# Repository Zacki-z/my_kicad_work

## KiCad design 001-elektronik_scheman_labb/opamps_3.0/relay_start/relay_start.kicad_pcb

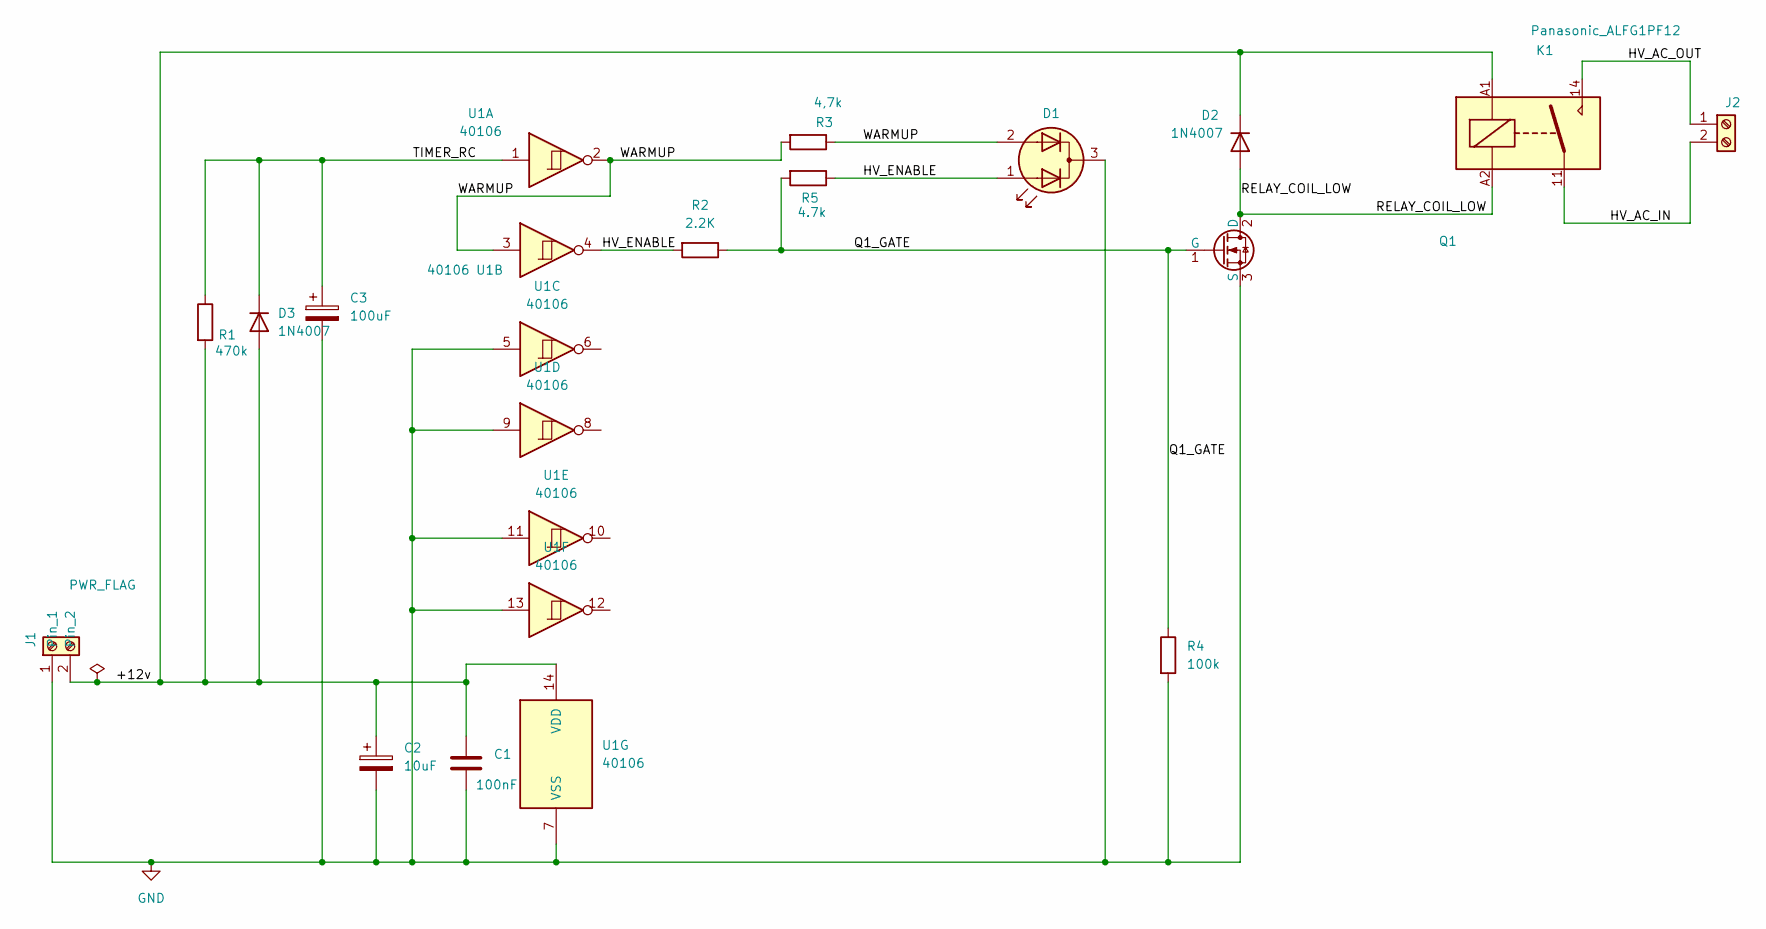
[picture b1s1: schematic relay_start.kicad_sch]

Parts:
C1: 100nF; CP_Radial_D5.0mm_P2.50mm
C2: 10uF; CP_Radial_D8.0mm_P3.50mm
C3: 100uF; CP_Radial_D8.0mm_P3.50mm
D1: LED_D5.0mm-3
D2, D3: 1N4007; D_DO-41_SOD81_P10.16mm_Horizontal
J1, J2: Screw_Terminal_01x02; TerminalBlock_MaiXu_MX126-5.0-02P_1x02_P5.00mm
K1: Panasonic_ALFG1PF12; Relay_SPST_Panasonic_ALFG_FormA_CircularHoles
Q1: Q_NMOS_GDS; TO-92
R1: 470k; R_Axial_DIN0207_L6.3mm_D2.5mm_P7.62mm_Horizontal
R2: 2.2K; R_Axial_DIN0207_L6.3mm_D2.5mm_P7.62mm_Horizontal
R3: 4,7k; R_Axial_DIN0207_L6.3mm_D2.5mm_P7.62mm_Horizontal
R4: 100k; R_Axial_DIN0207_L6.3mm_D2.5mm_P7.62mm_Horizontal
R5: 4.7k; R_Axial_DIN0207_L6.3mm_D2.5mm_P7.62mm_Horizontal
U1: 40106; CERDIP-14_W7.62mm_SideBrazed

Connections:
/+12v: C1.1, C2.1, D2.1 (K), D3.2 (A), J1.2, K1.A1, R1.2, U1.14 (VDD)
/HV_AC_IN: J2.2, K1.11
/HV_AC_OUT: J2.1, K1.14
/HV_ENABLE: D1.1 (A1), R2.2, R5.1, U1.4
/Q1_GATE: Q1.1 (G), R2.1, R4.1, R5.2
/RELAY_COIL_LOW: D2.2 (A), K1.A2, Q1.2 (D)
/TIMER_RC: C3.1, D3.1 (K), R1.1, U1.1
/WARMUP: D1.2 (A2), R3.1, R3.2, U1.2, U1.3
GND: C1.2, C2.2, C3.2, D1.3 (K), J1.1, Q1.3 (S), R4.2, U1.5, U1.7 (VSS), U1.9, U1.11, U1.13

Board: 2 copper layers, 16 parts (0 on the bottom side), 9 nets, no tracks yet.

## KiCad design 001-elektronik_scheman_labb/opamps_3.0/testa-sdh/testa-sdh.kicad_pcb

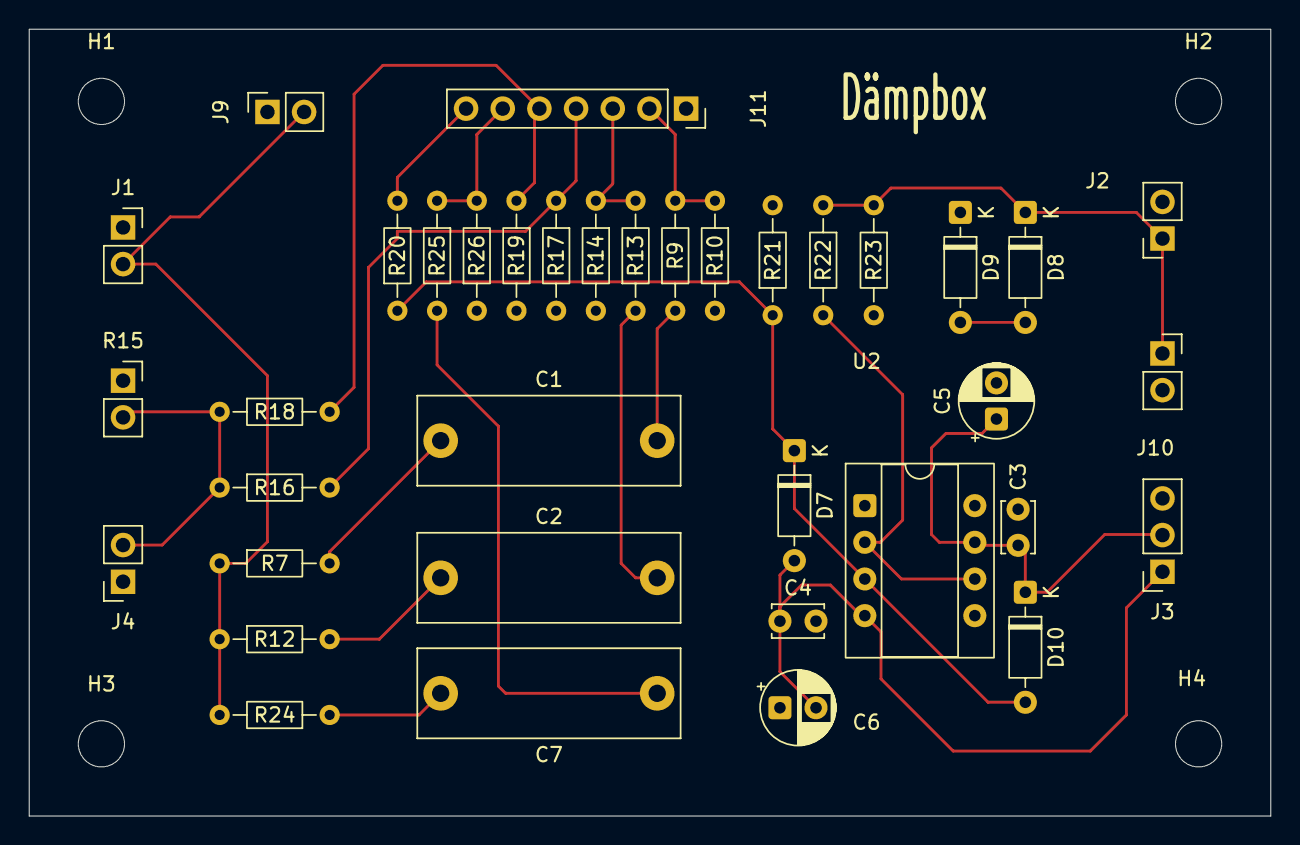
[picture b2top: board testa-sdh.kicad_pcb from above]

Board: 2 copper layers, 86.0 x 54.5 mm, 41 parts (0 on the bottom side), 21 nets.

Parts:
C1, C2: 100 nF 630v; C_Rect_L18.0mm_W6.0mm_P15.00mm_FKS3_FKP3
C3, C4: 100 nF; C_Disc_D3.4mm_W2.1mm_P2.50mm
C5, C6: 10 uF; CP_Radial_D5.0mm_P2.50mm
C7: 100 nF 630V; C_Rect_L18.0mm_W6.0mm_P15.00mm_FKS3_FKP3
D7, D10: 1N4148; D_DO-35_SOD27_P7.62mm_Horizontal
D8, D9: BZX55C5V1; D_DO-35_SOD27_P7.62mm_Horizontal
H1, H2, H3, H4: MountingHole; MountingHole_3.2mm_M3
J1: Test_probe; PinSocket_1x02_P2.54mm_Vertical
J2: TO_Focusrite_input; PinSocket_1x02_P2.54mm_Vertical
J3: OP_AMP_PWR; PinSocket_1x03_P2.54mm_Vertical
J4: Speaker; PinSocket_1x02_P2.54mm_Vertical
J9, J10: Mätinstrument; PinSocket_1x02_P2.54mm_Vertical
J11: J_SW_SIGNAL; PinSocket_1x07_P2.54mm_Vertical
R7, R12, R21, R26: 1M; R_Axial_DIN0204_L3.6mm_D1.6mm_P7.62mm_Horizontal
R9, R13: 953k; R_Axial_DIN0204_L3.6mm_D1.6mm_P7.62mm_Horizontal
R10: 20K; R_Axial_DIN0204_L3.6mm_D1.6mm_P7.62mm_Horizontal
R14: 274k; R_Axial_DIN0204_L3.6mm_D1.6mm_P7.62mm_Horizontal
R15: 8 50W; PinSocket_1x02_P2.54mm_Vertical
R16, R23: 100k; R_Axial_DIN0204_L3.6mm_D1.6mm_P7.62mm_Horizontal
R17: 1k; R_Axial_DIN0204_L3.6mm_D1.6mm_P7.62mm_Horizontal
R18: 90,9k; R_Axial_DIN0204_L3.6mm_D1.6mm_P7.62mm_Horizontal
R19: 10k; R_Axial_DIN0204_L3.6mm_D1.6mm_P7.62mm_Horizontal
R20: 20k; R_Axial_DIN0204_L3.6mm_D1.6mm_P7.62mm_Horizontal
R22: 330R; R_Axial_DIN0204_L3.6mm_D1.6mm_P7.62mm_Horizontal
R24, R25: 10K; R_Axial_DIN0204_L3.6mm_D1.6mm_P7.62mm_Horizontal
U2: OPA134; CERDIP-8_W7.62mm_SideBrazed_Socket

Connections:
/INTPUT: J1.2, J9.2, R7.1, R12.1, R24.2
/INT_1_10: C2.1, R12.2
/INT_1_10_OUT: J11.3, R13.2, R14.1
/INT_1_100: C1.1, R7.2
/INT_1_100_OUT: J11.2, R9.2, R10.1
/LOW_1_1: C7.2, R24.1
/LOW_1_1_OUT: J11.6, R25.1, R26.2
/SPK_1_10_OUT: J11.5, R18.2, R19.1
/SPK_1_100: J4.2, R15.2, R16.1, R18.1
/SPK_1_100_OUT: J11.4, R16.2, R17.1
/sound-card/12V+: C3.1, C5.1, D10.1 (K), J3.2, U2.7 (V+)
/sound-card/12V-: C4.1, C6.2, D7.2 (A), J3.1, U2.4 (V-)
/sound-card/OP_AMP_OUT: R22.2, U2.2 (-), U2.6
/sound-card/audio_out: D8.1 (K), J2.1, J10.1, R22.1, R23.1
MEASURE_GND: C3.2, C4.2, C5.2, C6.1, D9.1 (K), J1.1, J2.2, J3.3, J4.1, J9.1, J10.2, R10.2, R14.2, R15.1, R17.2, R19.2, R21.2, R23.2, R26.1
MEASURE_SIGNAL: J11.7, R20.2
unnamed: C1.2, R9.1
unnamed: C2.2, R13.1
unnamed: C7.1, R25.2
unnamed: D8.2 (A), D9.2 (A)
unnamed: D7.1 (K), D10.2 (A), R20.1, R21.1, U2.3 (+)

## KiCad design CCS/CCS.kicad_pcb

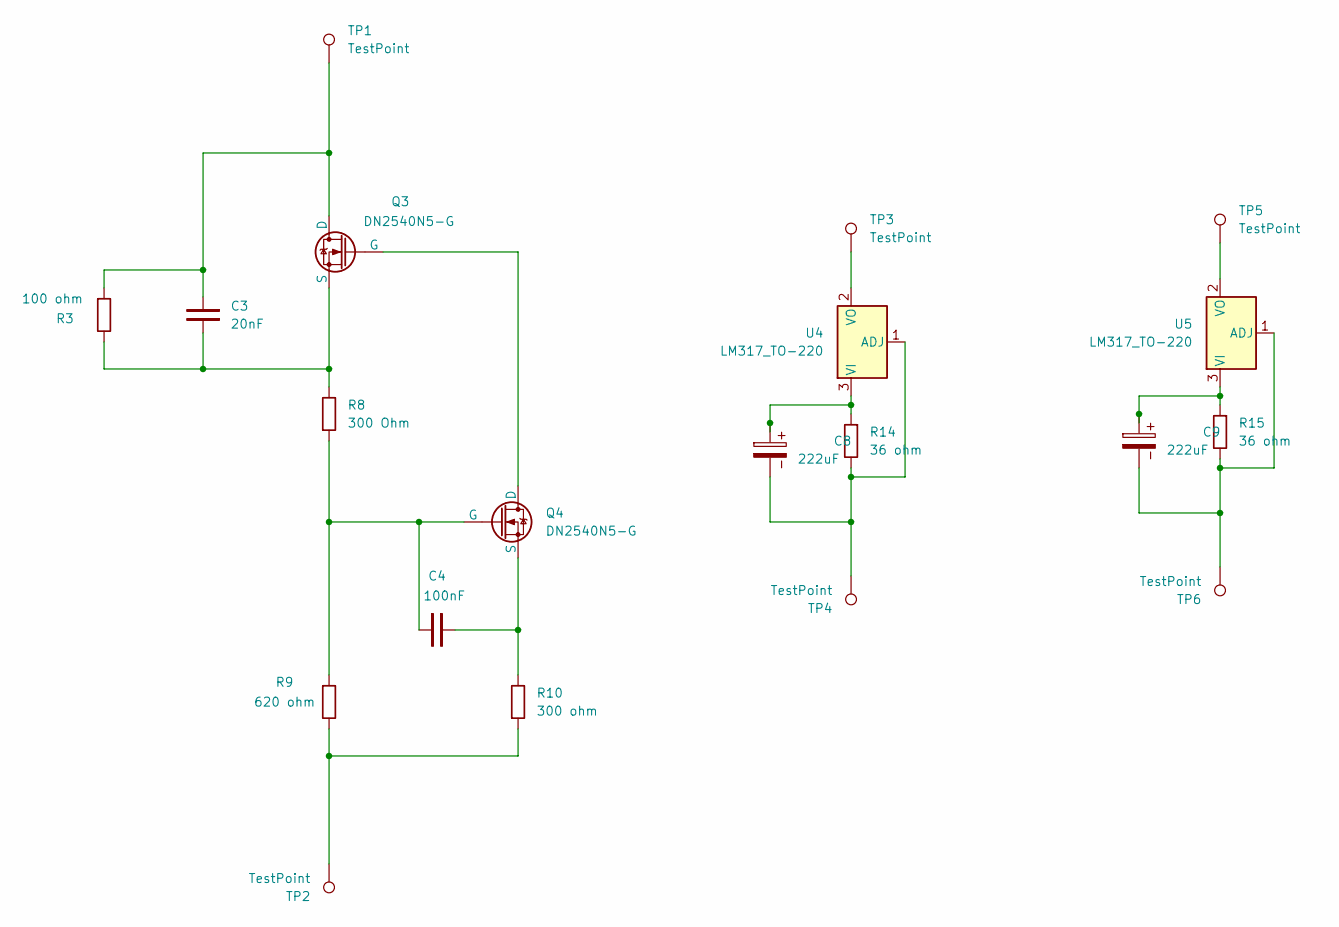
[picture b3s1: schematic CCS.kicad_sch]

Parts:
C3: 20nF; C_Disc_D3.0mm_W2.0mm_P2.50mm
C4: 100nF; C_Disc_D3.0mm_W2.0mm_P2.50mm
C8, C9: 222uF; CP_Radial_D5.0mm_P2.00mm
Q3, Q4: DN2540N5-G; TO-220-3_Vertical
R3: 100 ohm; R_Axial_DIN0207_L6.3mm_D2.5mm_P10.16mm_Horizontal
R8: 300 Ohm; R_Axial_DIN0207_L6.3mm_D2.5mm_P10.16mm_Horizontal
R9: 620 ohm; R_Axial_DIN0207_L6.3mm_D2.5mm_P10.16mm_Horizontal
R10: 300 ohm; R_Axial_DIN0207_L6.3mm_D2.5mm_P10.16mm_Horizontal
R14, R15: 36 ohm; R_Axial_DIN0207_L6.3mm_D2.5mm_P10.16mm_Horizontal
TP1, TP2, TP3, TP4, TP5, TP6: TestPoint; Pin_D1.3mm_L10.0mm_W3.5mm_Flat
U4, U5: LM317_TO-220; TO-220-3_Vertical

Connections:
unnamed: C3.1, Q3.2 (D), R3.1, TP1.1
unnamed: Q3.1 (G), Q4.2 (D)
unnamed: C3.2, Q3.3 (S), R3.2, R8.2
unnamed: C4.1, Q4.1 (G), R8.1, R9.1
unnamed: C4.2, Q4.3 (S), R10.2
unnamed: R9.2, R10.1, TP2.1
unnamed: C8.2, R14.2, TP4.1, U4.1 (ADJ)
unnamed: C8.1, R14.1, U4.3 (VI)
unnamed: TP3.1, U4.2 (VO)
unnamed: C9.2, R15.2, TP6.1, U5.1 (ADJ)
unnamed: C9.1, R15.1, U5.3 (VI)
unnamed: TP5.1, U5.2 (VO)

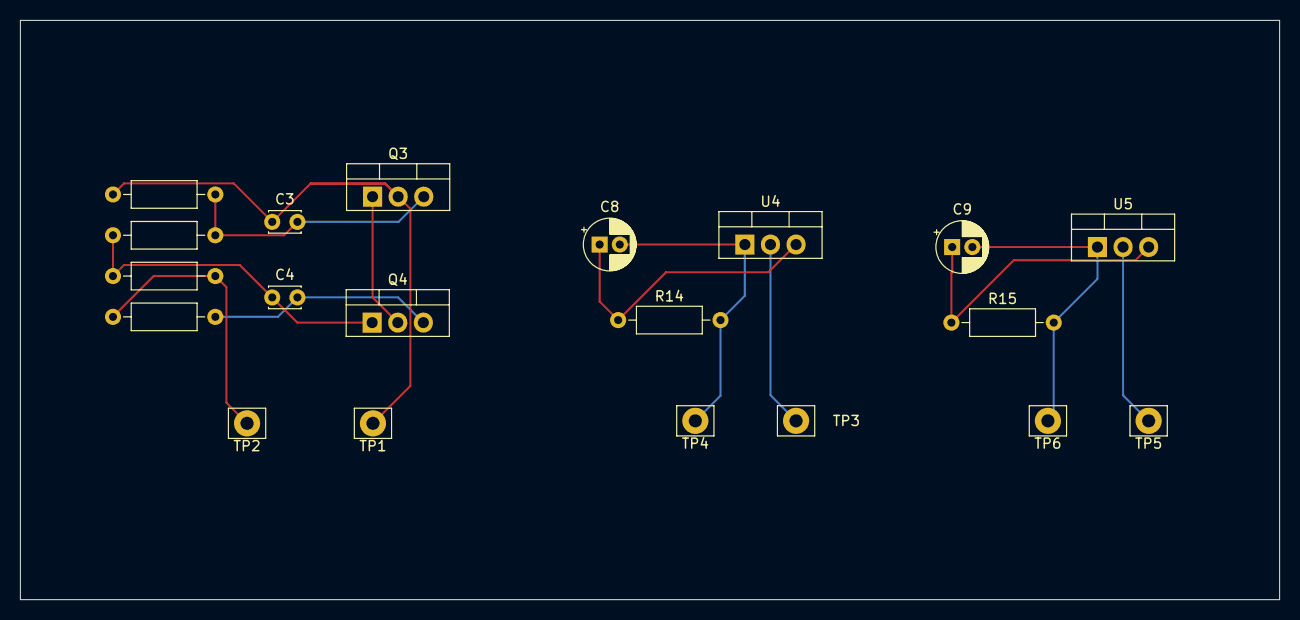
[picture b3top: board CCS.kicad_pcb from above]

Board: 2 copper layers, 125.0 x 57.5 mm, 20 parts (0 on the bottom side), 12 nets.

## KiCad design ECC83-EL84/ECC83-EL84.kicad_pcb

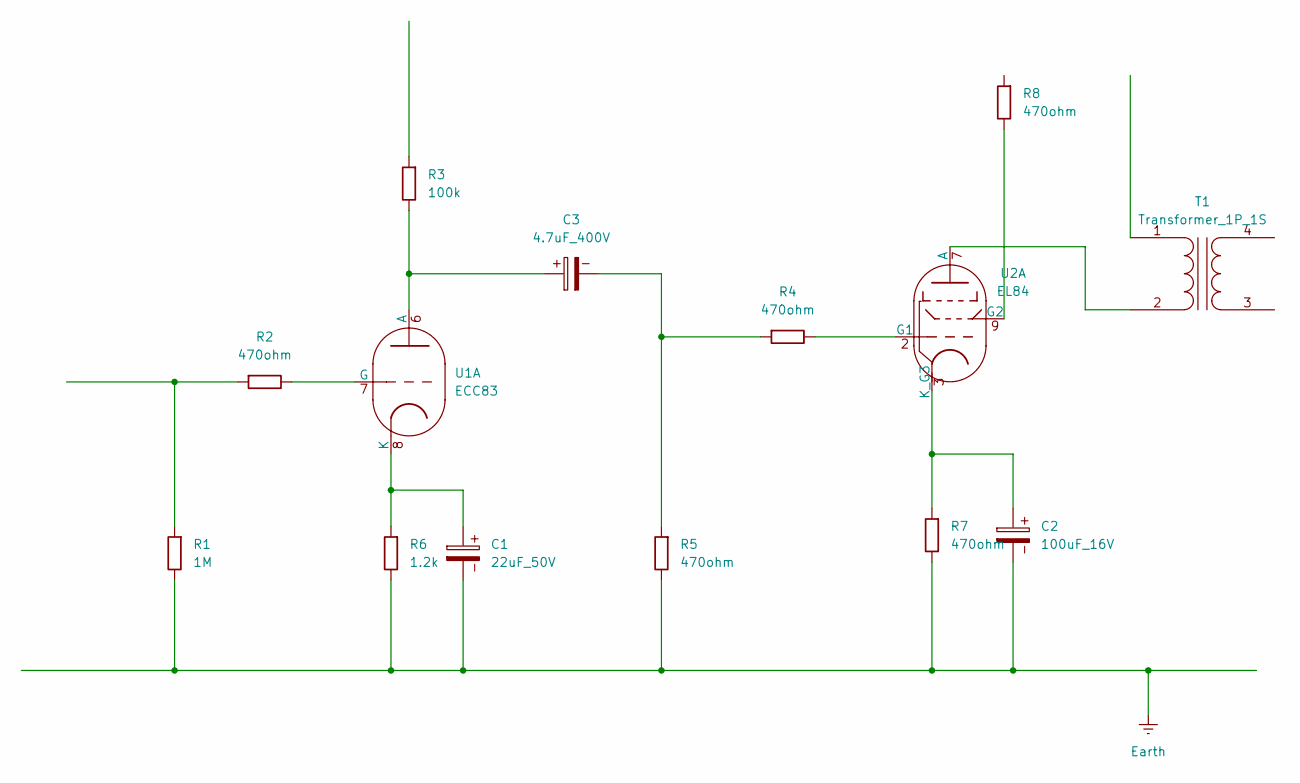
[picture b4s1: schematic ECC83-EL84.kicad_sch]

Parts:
C1: 22uF_50V; CP_Radial_D5.0mm_P2.00mm
C2: 100uF_16V; CP_Radial_D5.0mm_P2.00mm
C3: 4.7uF_400V; CP_Radial_D10.0mm_P5.00mm
R1: 1M; R_Axial_DIN0207_L6.3mm_D2.5mm_P10.16mm_Horizontal
R2, R4, R5, R7, R8: 470ohm; R_Axial_DIN0207_L6.3mm_D2.5mm_P10.16mm_Horizontal
R3: 100k; R_Axial_DIN0207_L6.3mm_D2.5mm_P10.16mm_Horizontal
R6: 1.2k; R_Axial_DIN0207_L6.3mm_D2.5mm_P10.16mm_Horizontal
T1: Transformer_1P_1S
U1: ECC83; Valve_Noval_P
U2: EL84; Valve_Noval_P

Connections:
Earth: C1.2, C2.2, R1.2, R5.2, R6.2, R7.2
unnamed: C3.2, R4.1, R5.1
unnamed: R1.1, R2.1
unnamed: T1.2 (AB), U2.7 (A)
unnamed: C3.1, R3.2, U1.6 (A)
unnamed: R2.2, U1.7 (G)
unnamed: C1.1, R6.1, U1.8 (K)
unnamed: R4.2, U2.2 (G1)
unnamed: R8.2, U2.9 (G2)
unnamed: C2.1, R7.1, U2.3 (K_G3)

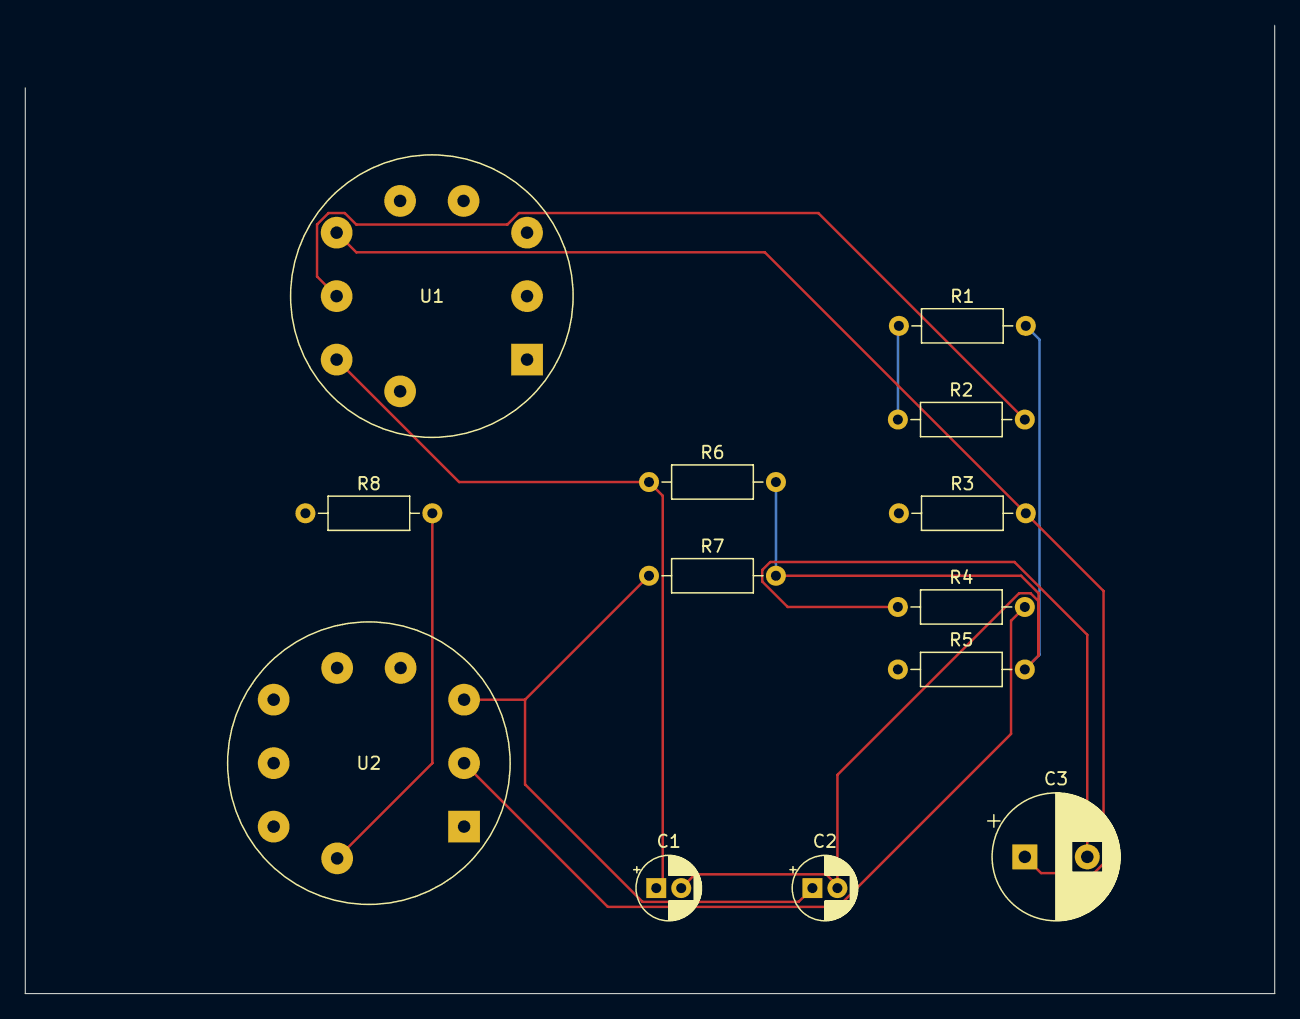
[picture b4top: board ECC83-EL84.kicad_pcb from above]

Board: 2 copper layers, 100.0 x 77.5 mm, 13 parts (0 on the bottom side), 9 nets.

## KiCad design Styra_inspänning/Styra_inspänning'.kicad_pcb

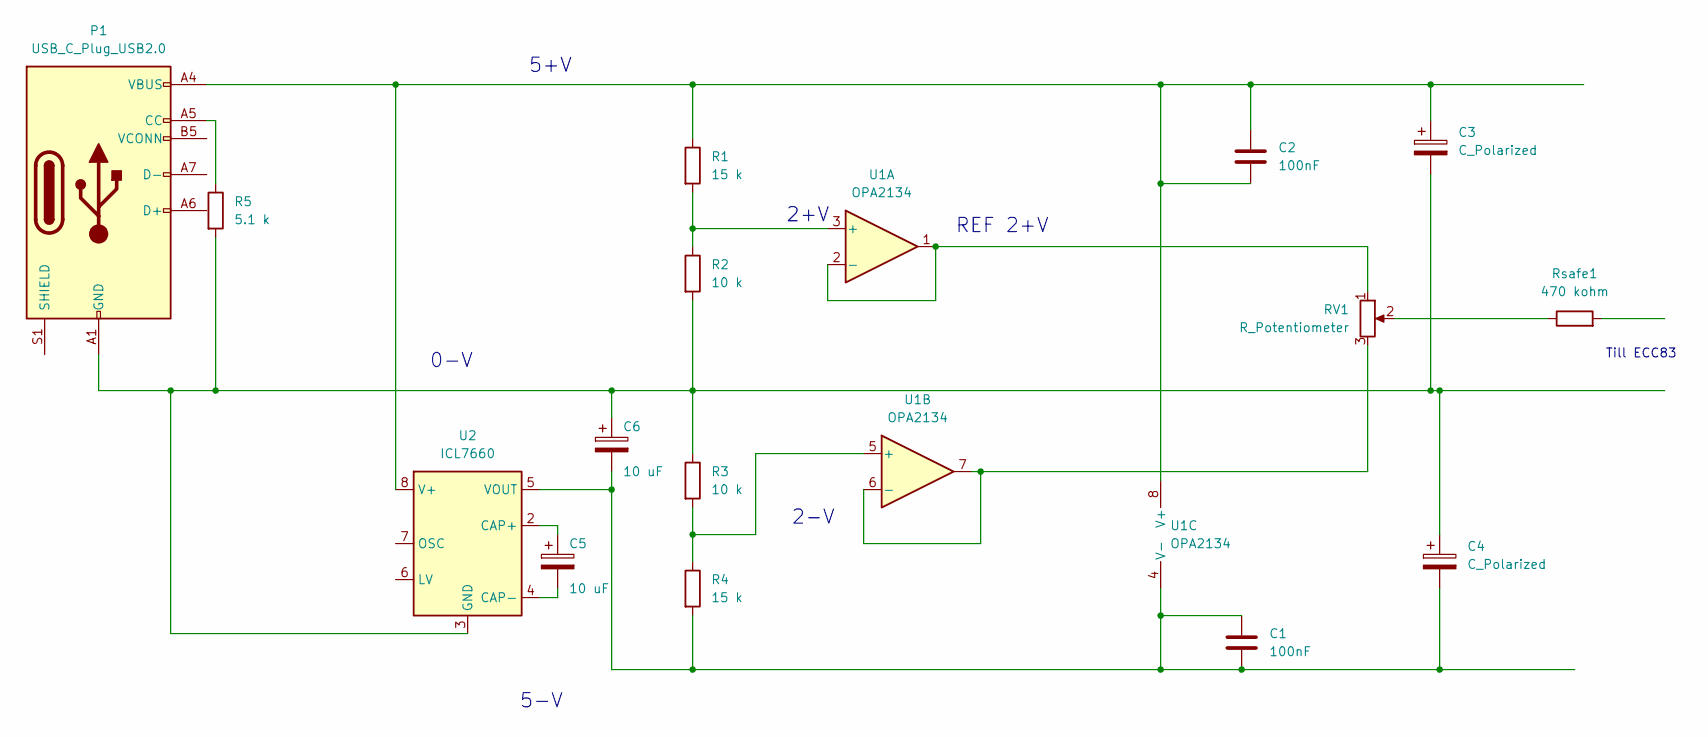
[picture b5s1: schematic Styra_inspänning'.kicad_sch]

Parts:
C1, C2: 100nF; CP_Radial_D13.0mm_P7.50mm
C3, C4: C_Polarized; CP_Radial_D13.0mm_P7.50mm
C5, C6: 10 uF; CP_Radial_D13.0mm_P7.50mm
P1: USB_C_Plug_USB2.0; USB_C_Receptacle_Amphenol_124019772112A
R1, R4: 15 k; R_Axial_DIN0614_L14.3mm_D5.7mm_P15.24mm_Horizontal
R2, R3: 10 k; R_Axial_DIN0614_L14.3mm_D5.7mm_P15.24mm_Horizontal
R5: 5.1 k; R_Axial_DIN0614_L14.3mm_D5.7mm_P15.24mm_Horizontal
RV1: R_Potentiometer; Potentiometer_Bourns_3266Z_Horizontal
Rsafe1: 470 kohm; R_Axial_DIN0614_L14.3mm_D5.7mm_P15.24mm_Horizontal
U1: OPA2134; DIP-8_W10.16mm
U2: ICL7660; DIP-8_W10.16mm

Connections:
unnamed: P1.A5 (CC), R5.1
unnamed: RV1.2, Rsafe1.1
unnamed: R1.2, R2.1, U1.3 (+)
unnamed: RV1.1, U1.1, U1.2 (-)
unnamed: R3.2, R4.1, U1.5 (+)
unnamed: RV1.3, U1.6 (-), U1.7
unnamed: C2.1, C2.2, C3.1, P1.A4 (VBUS), P1.A9 (VBUS), P1.B4 (VBUS), P1.B9 (VBUS), R1.1, U1.8 (V+), U2.8 (V+)
unnamed: C1.1, C1.2, C4.2, C6.2, R4.2, U1.4 (V-), U2.5 (VOUT)
unnamed: C5.1, U2.2 (CAP+)
unnamed: C5.2, U2.4 (CAP-)
unnamed: C3.2, C4.1, C6.1, P1.A1 (GND), P1.A12 (GND), P1.B1 (GND), P1.B12 (GND), R2.2, R3.1, R5.2, U2.3 (GND)

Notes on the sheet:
2-V
5+V
0-V
2+V
Till ECC83
5-V
REF 2+V

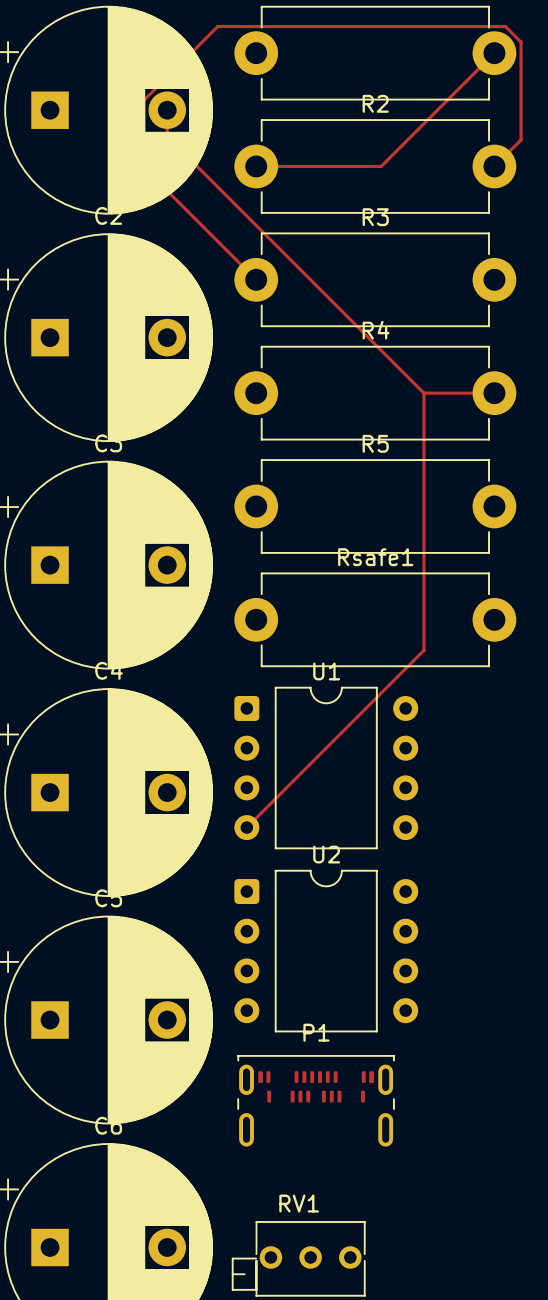
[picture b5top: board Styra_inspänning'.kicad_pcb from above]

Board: 2 copper layers, 16 parts (0 on the bottom side), 11 nets.

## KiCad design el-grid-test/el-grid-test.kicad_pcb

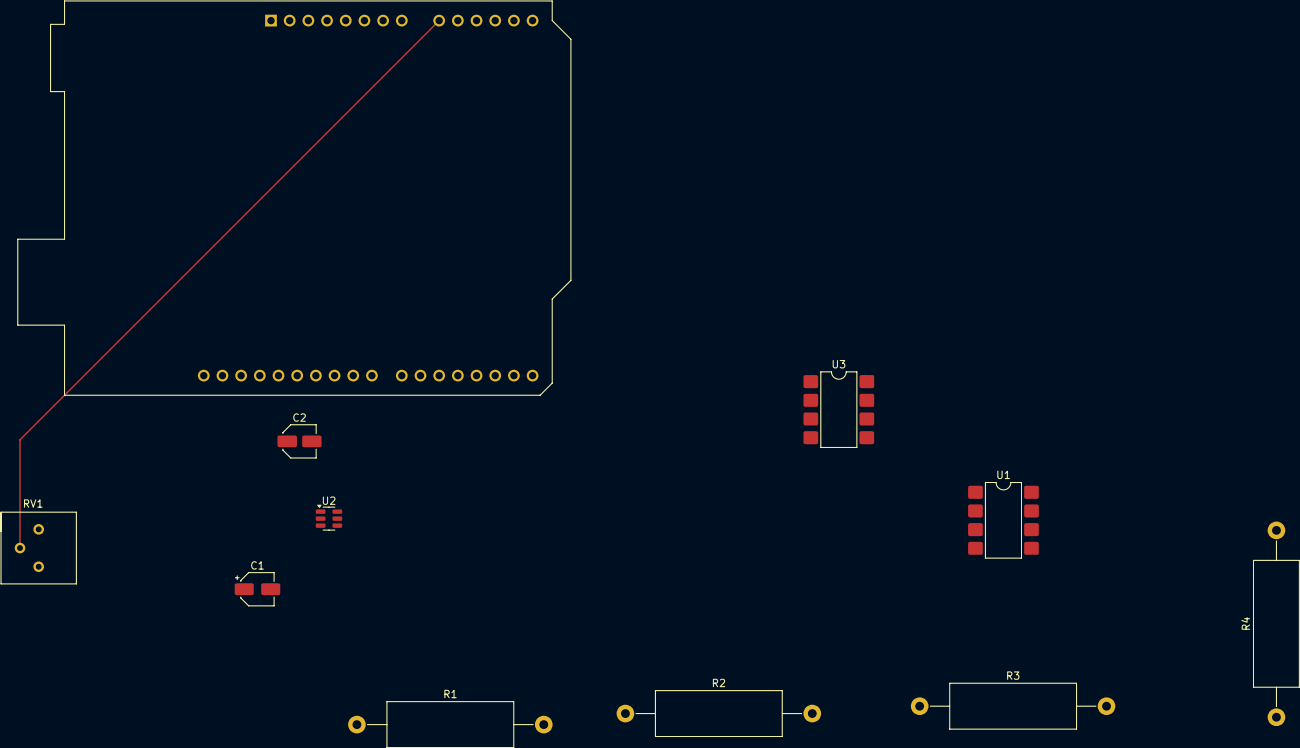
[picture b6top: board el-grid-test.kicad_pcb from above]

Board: 2 copper layers, 11 parts (0 on the bottom side), 13 nets.

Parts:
A1: Arduino_UNO_R3
C1: 10 uf; CP_Elec_4x5.8
C2: 10 uf; C_Elec_4x5.4
R1, R2, R3, R4: 10k; R_Axial_DIN0617_L17.0mm_D6.0mm_P25.40mm_Horizontal
RV1: R_Potentiometer; Potentiometer_Bourns_3296P_Horizontal
U1: TL072; SMDIP-8_W7.62mm
U2: MCP4725xxx-xCH; SOT-23-6
U3: ICL7660; SMDIP-8_W7.62mm

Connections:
Earth: A1.7 (GND), C2.2, R4.1, RV1.3, U2.2 (VSS), U3.3 (GND)
unnamed: A1.5 (+5V), R3.2, RV1.1, U1.8 (V+), U2.3 (VDD), U3.8 (V+)
unnamed: A1.9 (A0), RV1.2
unnamed: R2.1, U1.1
unnamed: U1.3 (+), U1.6 (-), U1.7
unnamed: R1.1, R2.2, U1.2 (-)
unnamed: R3.1, R4.2, U1.5 (+)
unnamed: C2.1, U1.4 (V-), U3.5 (VOUT)
unnamed: A1.14 (SCL/A5), U2.5 (SCL)
unnamed: A1.13 (SDA/A4), U2.4 (SDA)
unnamed: R1.2, U2.1 (VOUT)
unnamed: C1.1, U3.2 (CAP+)
unnamed: C1.2, U3.4 (CAP-)

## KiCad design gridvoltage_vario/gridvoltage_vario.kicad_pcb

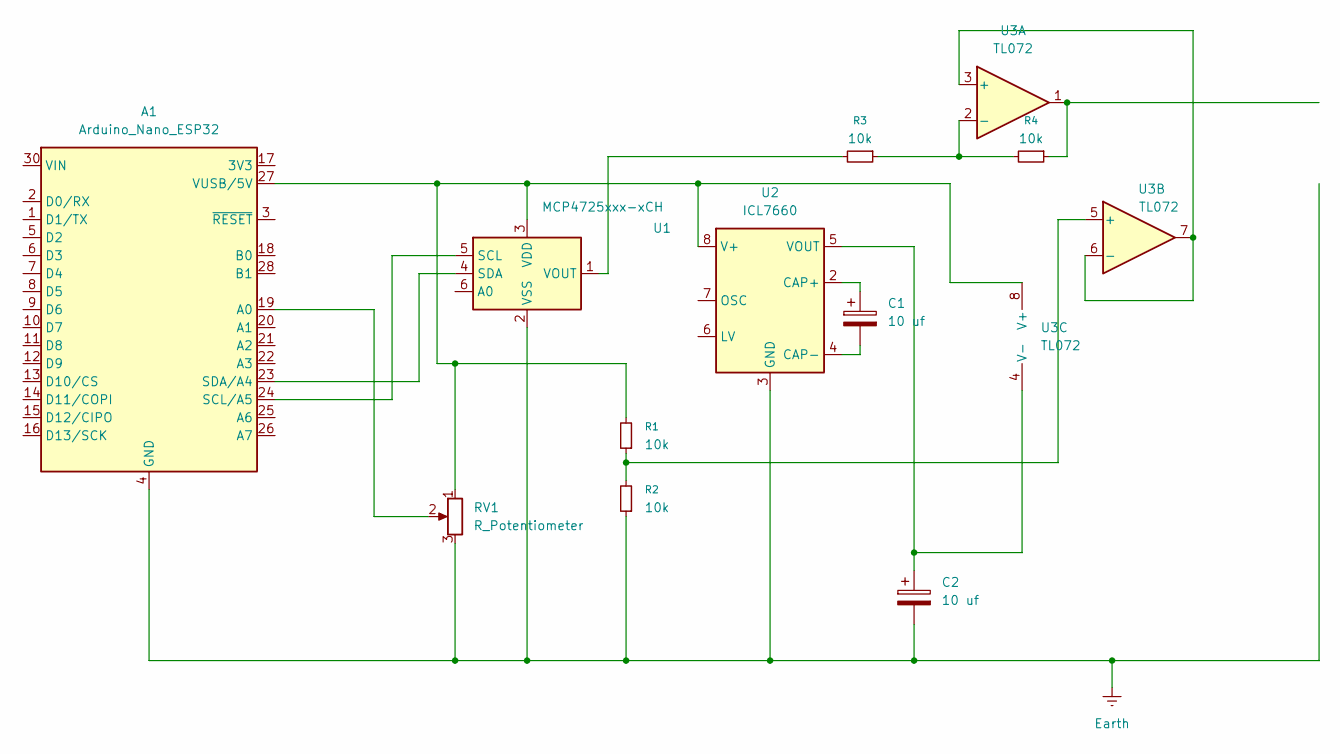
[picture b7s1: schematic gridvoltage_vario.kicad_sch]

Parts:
A1: Arduino_Nano_ESP32; Arduino_Nano
C1: 10 uf; CP_Elec_4x5.8
C2: 10 uf; C_Elec_4x5.4
R1, R2, R3, R4: 10k; R_Axial_DIN0617_L17.0mm_D6.0mm_P25.40mm_Horizontal
RV1: R_Potentiometer; Potentiometer_Bourns_3296P_Horizontal
U1: MCP4725xxx-xCH; Molex_KK-254_AE-6410-06A_1x06_P2.54mm_Vertical
U2: ICL7660; SMDIP-8_W7.62mm
U3: TL072; SMDIP-8_W7.62mm

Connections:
Earth: A1.4 (GND), A1.29 (GND), C2.2, R2.1, RV1.3, U1.2 (VSS), U2.3 (GND)
unnamed: A1.19 (A0), RV1.2
unnamed: A1.24 (SCL/A5), U1.5 (SCL)
unnamed: A1.23 (SDA/A4), U1.4 (SDA)
unnamed: A1.27 (VUSB/5V), R1.2, RV1.1, U1.3 (VDD), U2.8 (V+), U3.8 (V+)
unnamed: R4.1, U3.1
unnamed: R3.2, U1.1 (VOUT)
unnamed: C1.1, U2.2 (CAP+)
unnamed: C1.2, U2.4 (CAP-)
unnamed: C2.1, U2.5 (VOUT), U3.4 (V-)
unnamed: U3.3 (+), U3.6 (-), U3.7
unnamed: R3.1, R4.2, U3.2 (-)
unnamed: R1.1, R2.2, U3.5 (+)

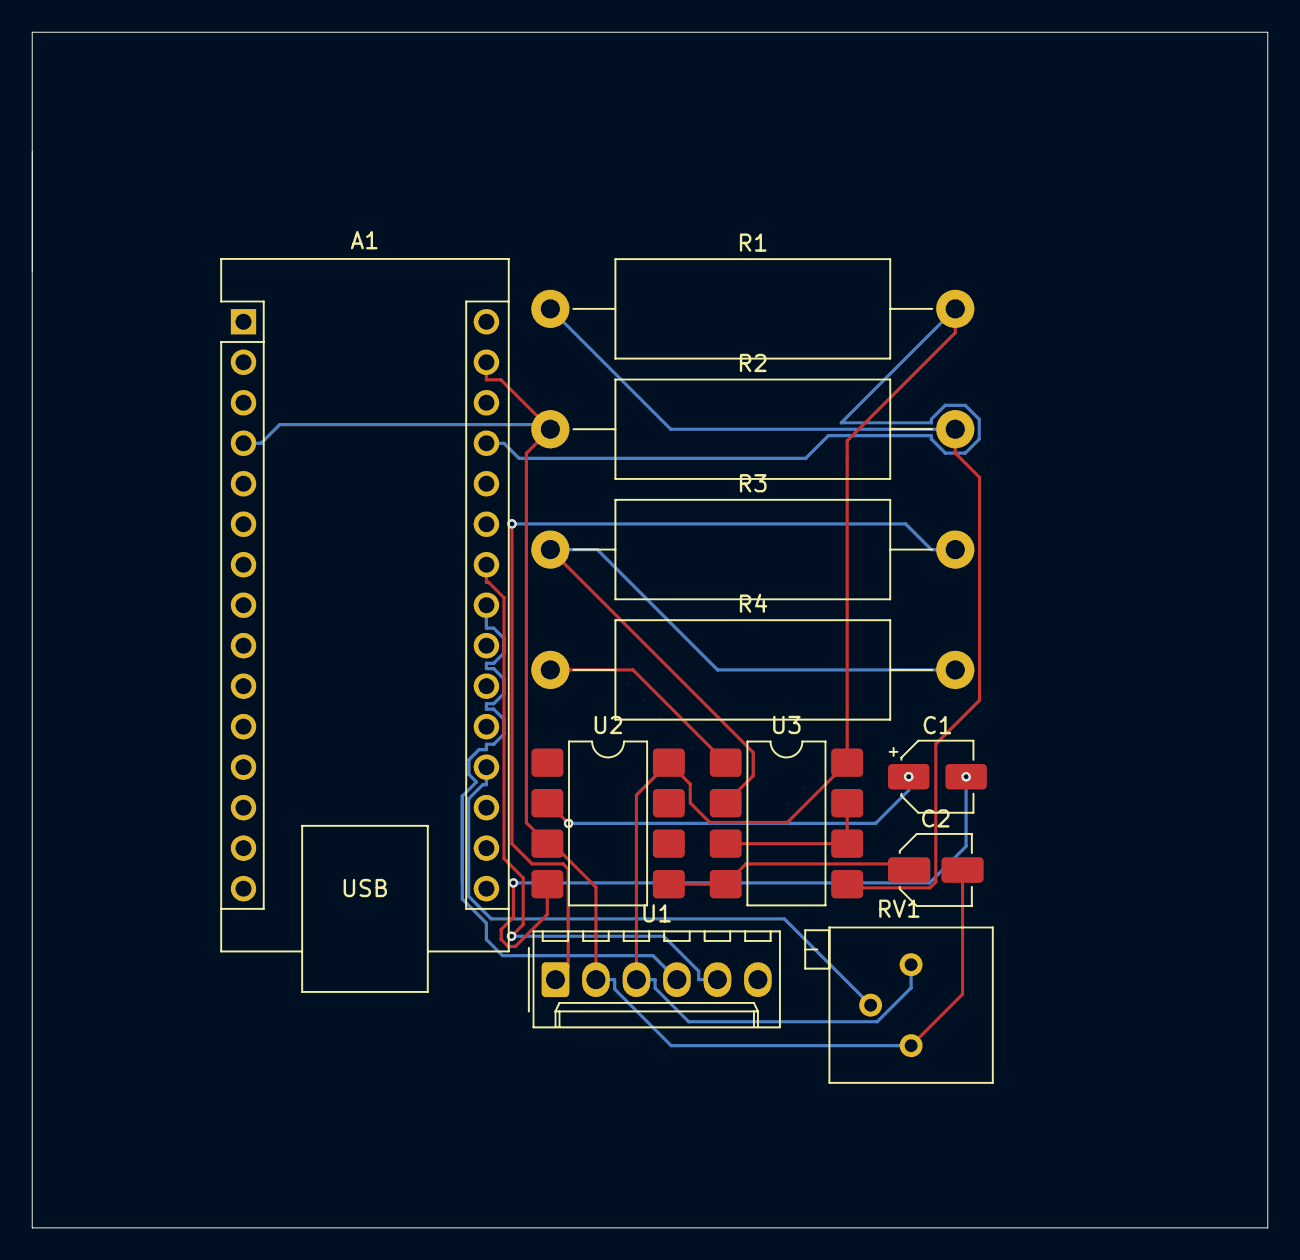
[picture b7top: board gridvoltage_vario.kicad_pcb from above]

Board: 2 copper layers, 77.5 x 75.0 mm, 11 parts (0 on the bottom side), 13 nets.
